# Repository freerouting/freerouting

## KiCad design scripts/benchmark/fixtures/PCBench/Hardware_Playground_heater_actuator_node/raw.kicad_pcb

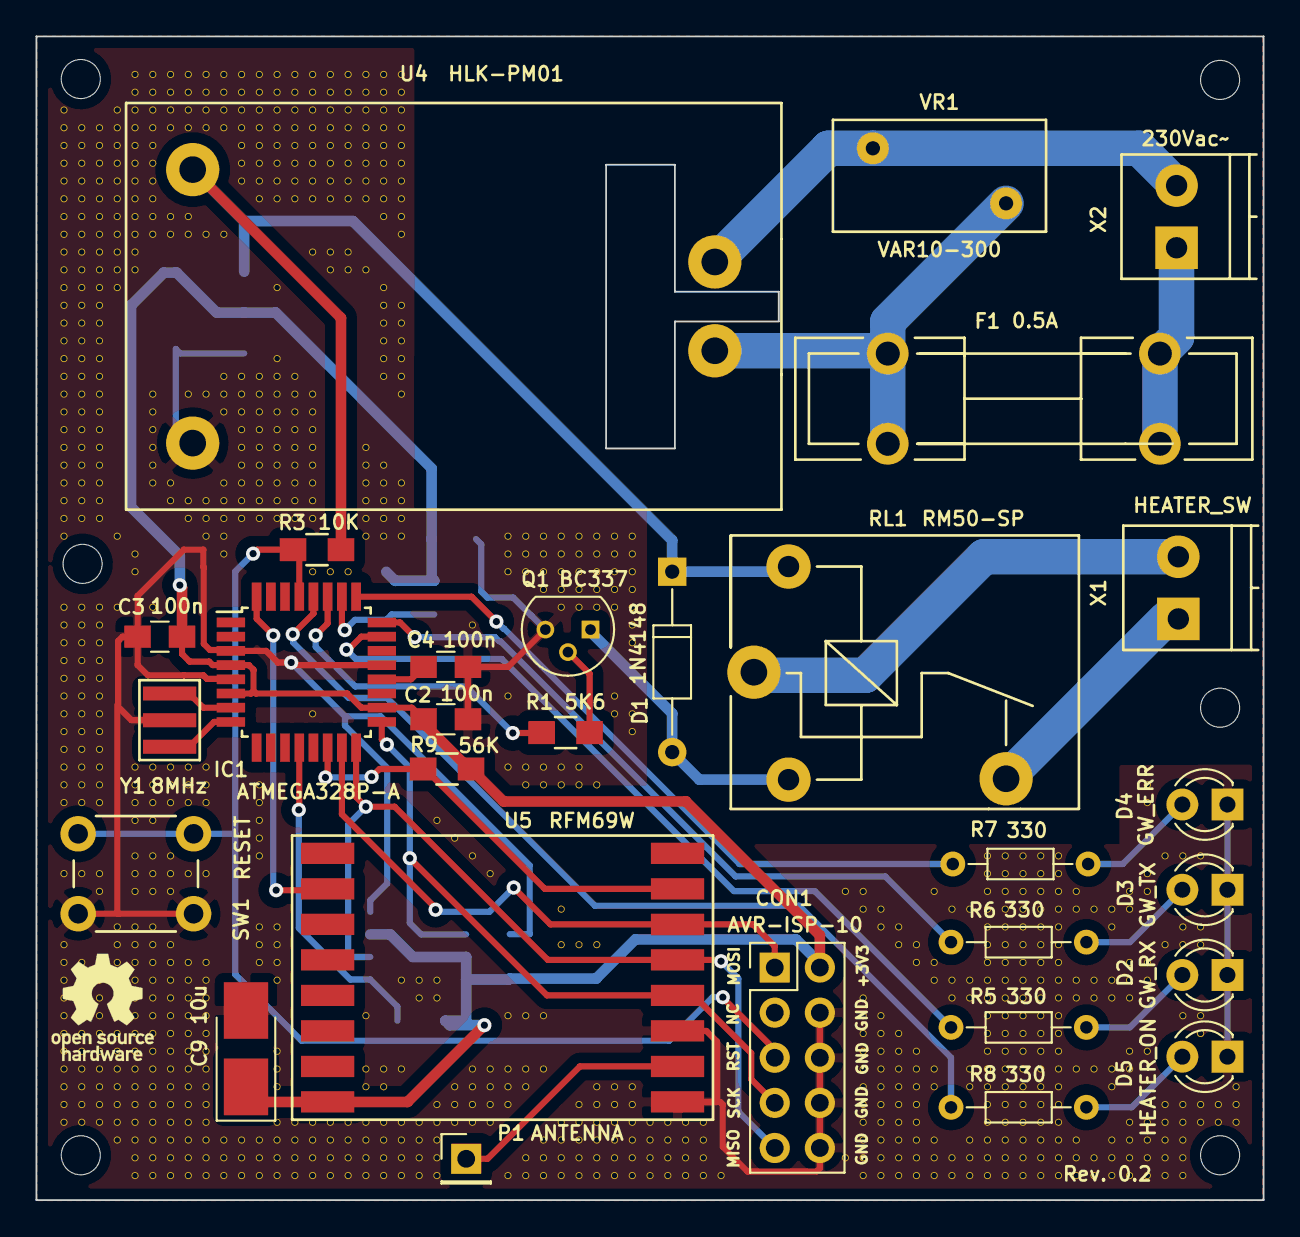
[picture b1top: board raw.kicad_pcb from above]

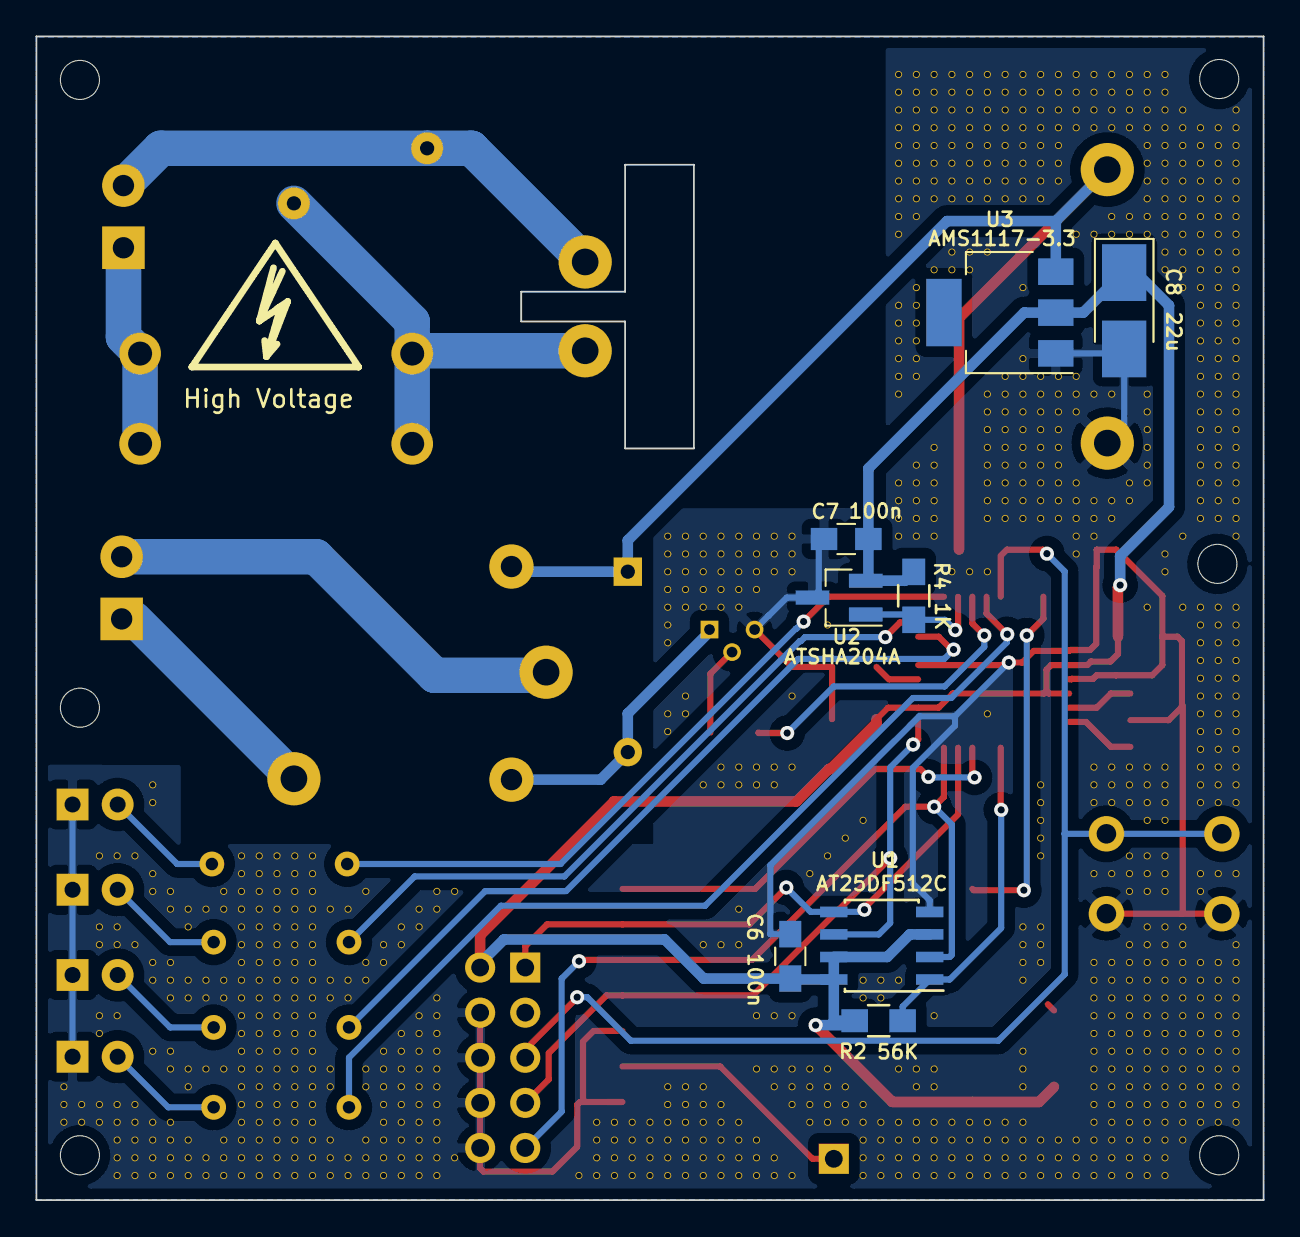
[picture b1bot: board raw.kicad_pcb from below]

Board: 2 copper layers, 69.1 x 65.5 mm, 982 parts (8 on the bottom side), 31 nets.

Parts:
C2, C3, C4, C6, C7: 100n; C_0805_HandSoldering
C8: 22u; CP_Tantalum_Case-B_EIA-3528-21_Hand
C9: 10u; CP_Tantalum_Case-B_EIA-3528-21_Hand
CON1: AVR-ISP-10; Pin_Header_Straight_2x05_Pitch2.54mm
D1: 1N4148; D_DO-35_SOD27_P10.16mm_Horizontal
D2: GW_RX; LED_D3.0mm
D3: GW_TX; LED_D3.0mm
D4: GW_ERR; LED_D3.0mm
D5: HEATER_ON; LED_D3.0mm
F1: 0.5A; Fuseholder5x20_horiz_open_lateral_Type-II
IC1: ATMEGA328P-A; TQFP-32_7x7mm_Pitch0.8mm
P1: ANTENNA; Pin_Header_Straight_1x01_Pitch2.54mm
Q1: BC337; TO-92_Molded_Narrow
R1: 5K6; R_0805_HandSoldering
R2, R9: 56K; R_0805_HandSoldering
R3: 10K; R_0805_HandSoldering
R4: 1K; R_0805_HandSoldering
R5, R6, R7, R8: 330; R_Axial_DIN0204_L3.6mm_D1.6mm_P7.62mm_Horizontal
RL1: RM50-SP; RM50_SP
SW1: RESET; SW_PUSH_6mm
U1: AT25DF512C; SOIC-8_3.9x4.9mm_Pitch1.27mm
U2: ATSHA204A; SOT-23_Handsoldering
U3: AMS1117-3.3; SOT-223
U4: HLK-PM01
U5: RFM69W; RFM69HW_SMD_Handsoldering
V10_6, V10_7, V10_8, V10_9, V10_10, V10_11, V10_12, V10_13, V10_14, V10_15, V10_16, V10_17, V10_18, V10_19, V10_20, V10_21, V10_22, V10_23, V10_24, V10_25, V10_26, V10_27, V10_28, V10_29, V10_30, V10_34, V10_35, V10_36, V10_37, V10_38, V10_39, V10_40, V10_41, V10_42, V10_43, V10_44, V10_45, V10_49, V10_53, V10_54, V10_55, V10_56, V10_57, V10_58, V10_59, V10_60, V10_61, V10_62, V10_63, V11_7, V11_8, V11_9, V11_10, V11_11, V11_12, V11_13, V11_14, V11_15, V11_16, V11_17, V11_18, V11_19, V11_20, V11_21, V11_22, V11_23, V11_24, V11_25, V11_26, V11_27, V11_28, V11_29, V11_34, V11_35, V11_36, V11_37, V11_38, V11_39, V11_40, V11_41, V11_42, V11_43, V11_44, V11_45, V11_49, V11_54, V11_55, V11_56, V11_57, V11_58, V11_59, V11_60, V11_61, V11_62, V11_63, V12_7, V12_8, V12_9, V12_10, V12_11, V12_12, V12_13, V12_14, V12_15, V12_16, V12_17, V12_18, V12_19, V12_20, V12_21, V12_22, V12_23, V12_24, V12_25, V12_26, V12_27, V12_28, V12_29, V12_34, V12_35, V12_36, V12_37, V12_38, V12_39, V12_40, V12_41, V12_42, V12_43, V12_44, V12_45, V12_49, V12_50, V12_54, V12_55, V12_56, V12_57, V12_58, V12_59, V12_60, V12_61, V12_62, V12_63, V13_6, V13_7, V13_8, V13_9, V13_10, V13_11, V13_12, V13_13, V13_14, V13_15, V13_16, V13_30, V13_34, V13_52, V13_53, V13_54, V13_55, V13_56, V13_57, V13_58, V13_59, V13_60, V13_61, V13_62, V13_63, V13_64, V14_4, V14_5, V14_6, V14_7, V14_8, V14_9, V14_10, V14_11, V14_12, V14_13, V14_14, V14_15, V14_31, V14_32, V14_43, V14_44, V14_45, V14_46, V14_48, V14_49, V14_50, V14_52, V14_53, V14_54, V14_55, V14_56, V14_57, V14_58, V14_59, V14_60, V14_61, V14_62, V14_63, V14_64, V14_65, V14_66, V15_4, V15_5, V15_6, V15_7, V15_8, V15_9, V15_10, V15_11, V15_12, V15_13, V15_22, V15_23, V15_24, V15_25, V15_26, V15_27, V15_34, V15_43, V15_44, V15_45, V15_46, V15_48, V15_49, V15_50, V15_52, V15_53, V15_54, V15_55, V15_56, V15_57, V15_58, V15_59, V15_60, V15_61, V15_62, V15_63, V15_64, V15_65, V15_66, V16_4, V16_5, V16_6, V16_7, V16_12, V16_13, V16_27, V16_28, V16_43, V16_44, V16_45, V16_48, V16_49, V16_50, V16_53, V16_54, V16_55, V16_56, V16_57, V16_58, V16_59, V16_60, V16_61, V16_62, V16_63, V16_64, V16_65, V16_66, V17_4, V17_5, V17_6, V17_7, V17_12, V17_13, V17_22, V17_28, V17_29, V17_43, V17_44, V17_45, V17_49, V17_54, V17_55, V17_56, V17_57, V17_58, V17_59, V17_60, V17_61, V17_62, V17_63, V17_64, V17_65, V17_66, V18_4, V18_5, V18_6, V18_7, V18_13, V18_22, V18_28, V18_29, V18_30, V18_43, V18_44, V18_45, V18_49, V18_54, V18_55, V18_56, V18_57, V18_58, V18_59, V18_60, V18_61, V18_62, V18_63, V18_64, V18_65, V18_66, V19_4, V19_5, V19_6, V19_7, V19_13, V19_21, V19_22, V19_23, V19_27, V19_28, V19_29, V19_30, V19_31, V19_64, V19_65, V19_66, V20_4, V20_5, V20_6, V20_7, V20_8, V20_9, V20_10, V20_21, V20_22, V20_23, V20_24, V20_25, V20_26, V20_27, V20_28, V20_29, V20_64, V20_65, V20_66, V21_4, V21_5, V21_6, V21_7, V21_8, V21_9, V21_10, V21_11, V21_21, V21_22, V21_23, V21_24, V21_25, V21_26, V21_27, V21_28, V21_29, V21_44, V21_45, V21_46, V21_47, V21_48, V21_52, V21_53, V21_54, V21_64, V21_65, V21_66, V22_4, V22_5, V22_6, V22_7, V22_8, V22_9, V22_10, V22_11, V22_16, V22_20, V22_21, V22_22, V22_23, V22_24, V22_25, V22_26, V22_27, V22_28, V22_29, V22_52, V22_53, V22_54, V22_55, V22_59, V22_60, V22_61, V22_63, V22_64, V22_65, V22_66, V23_4, V23_5, V23_6, V23_7, V23_8, V23_9, V23_10, V23_11, V23_21, V23_22, V23_23, V23_24, V23_25, V23_26, V23_27, V23_28, V23_29, V23_63, V23_64, V23_65, V23_66, V24_4, V24_5, V24_6, V24_7, V24_8, V24_9, V24_10, V24_11, V24_14, V24_22, V24_23, V24_24, V24_25, V24_26, V24_27, V24_28, V24_29, V24_32, V24_40, V24_63, V24_64, V24_65, V24_66, V25_4, V25_5, V25_6, V25_7, V25_8, V25_9, V25_10, V25_11, V25_14, V25_15, V25_32, V25_63, V25_64, V25_65, V25_66, V26_4, V26_5, V26_6, V26_7, V26_8, V26_9, V26_10, V26_11, V26_14, V26_15, V26_32, V26_63, V26_64, V26_65, V26_66, V27_4, V27_5, V27_6, V27_7, V27_8, V27_9, V27_10, V27_11, V27_15, V27_25, V27_26, V27_27, V27_28, V27_29, V27_30, V27_57, V27_60, V27_61, V27_63, V27_64, V27_65, V27_66, V28_4, V28_5, V28_6, V28_7, V28_8, V28_9, V28_10, V28_11, V28_12, V28_16, V28_17, V28_18, V28_19, V28_20, V28_21, V28_26, V28_27, V28_28, V28_29, V28_30, V28_60, V28_61, V28_63, V28_64, V28_65, V28_66, V29_4, V29_5, V29_6, V29_7, V29_8, V29_9, V29_10, V29_11, V29_12, V29_13, V29_17, V29_18, V29_19, V29_20, V29_21, V29_22, V29_27, V29_28, V29_29, V29_30, V29_55, V29_60, V29_63, V29_64, V29_65, V29_66, V30_55, V30_56, V30_63, V30_64, V30_65, V30_66, V31_46, V31_55, V31_56, V31_62, V31_63, V31_64, V31_65, V31_66, V32_47, V32_61, V32_62, V32_63, V33_35, V33_48, V33_60, V33_61, V33_62, V33_63, V34_49, V34_60, V34_61, V34_62, V34_63, V35_30, V35_31, V35_32, V35_39, V35_43, V35_57, V35_60, V35_61, V35_62, V35_66, V36_30, V36_31, V36_32, V36_43, V36_44, V36_57, V36_60, V36_61, V36_65, V36_66, V37_30, V37_31, V37_32, V37_33, V37_43, V37_44, V37_57, V37_60, V37_64, V37_65, V37_66, V38_30, V38_31, V38_32, V38_33, V38_34, V38_43, V38_44, V38_51, V38_53, V38_63, V38_64, V38_65, V38_66, V39_30, V39_31, V39_32, V39_33, V39_34, V39_43, V39_44, V39_53, V39_62, V39_63, V39_64, V39_65, V39_66, V40_30, V40_31, V40_32, V40_33, V40_34, V40_44, V40_53, V40_61, V40_62, V40_63, V40_64, V40_65, V40_66, V41_30, V41_31, V41_32, V41_33, V41_34, V41_39, V41_40, V41_61, V41_62, V41_63, V41_64, V41_65, V41_66, V42_30, V42_31, V42_32, V42_33, V42_34, V42_35, V42_36, V42_40, V42_41, V42_61, V42_62, V42_63, V42_64, V42_65, V42_66, V43_63, V43_64, V43_65, V43_66, V44_63, V44_64, V44_65, V44_66, V45_63, V45_64, V45_65, V45_66, V46_63, V46_64, V46_65, V46_66, V47_66, V54_50, V54_65, V55_50, V55_51, V55_56, V55_57, V55_58, V55_59, V55_60, V55_61, V55_62, V55_63, V55_64, V55_65, V55_66, V56_51, V56_52, V56_57, V56_58, V56_59, V56_60, V56_61, V56_62, V56_63, V56_64, V56_65, V56_66, V57_52, V57_53, V57_58, V57_59, V57_60, V57_61, V57_62, V57_63, V57_64, V57_65, V57_66, V58_53, V58_54, V58_59, V58_60, V58_61, V58_62, V58_63, V58_64, V58_65, V58_66, V59_50, V59_54, V59_55, V59_60, V59_61, V59_64, V59_65, V59_66, V60_51, V60_55, V60_56, V60_65, V60_66, V61_51, V61_55, V61_56, V61_60, V61_61, V61_64, V61_65, V61_66, V62_48, V62_49, V62_50, V62_51, V62_52, V62_53, V62_54, V62_55, V62_56, V62_57, V62_58, V62_59, V62_60, V62_61, V62_62, V62_63, V62_64, V62_65, V62_66, V63_48, V63_49, V63_50, V63_51, V63_52, V63_53, V63_54, V63_55, V63_56, V63_57, V63_58, V63_59, V63_60, V63_61, V63_62, V63_63, V63_64, V63_65, V63_66, V64_48, V64_49, V64_50, V64_51, V64_52, V64_53, V64_54, V64_55, V64_56, V64_57, V64_58, V64_59, V64_60, V64_61, V64_62, V64_63, V64_64, V64_65, V64_66, V65_48, V65_49, V65_50, V65_51, V65_52, V65_53, V65_54, V65_55, V65_56, V65_57, V65_58, V65_59, V65_60, V65_61, V65_62, V65_63, V65_64, V65_65, V65_66, V66_48, V66_49, V66_50, V66_51, V66_52, V66_53, V66_54, V66_55, V66_56, V66_57, V66_58, V66_59, V66_60, V66_61, V66_62, V66_63, V66_64, V66_65, V66_66, V67_50, V67_51, V67_55, V67_56, V67_60, V67_64, V67_65, V67_66, V68_51, V68_55, V68_56, V68_60, V68_65, V68_66, V69_51, V69_52, V69_55, V69_56, V69_60, V69_61, V69_64, V69_65, V69_66, V70_50, V70_51, V70_54, V70_55, V70_56, V70_59, V70_60, V70_63, V70_64, V70_65, V70_66, V71_44, V71_45, V71_49, V71_50, V71_54, V71_55, V71_59, V71_63, V71_64, V71_65, V71_66, V72_48, V72_53, V72_62, V72_63, V72_64, V72_65, V72_66, V73_48, V73_52, V73_53, V73_57, V73_62, V73_63, V73_64, V73_65, V73_66, V74_48, V74_52, V74_53, V74_57, V74_58, V74_62, V74_63, V75_62, V75_63, V76_61, V76_62, V76_63: AUTO_VIA; VIA_MATRIX
VR1: VAR10-300; RV_Disc_D12_W6.3_P7.5
X1: HEATER_SW; TerminalBlock_Pheonix_PT-3.5mm_2pol
X2: 230Vac~~; TerminalBlock_Pheonix_PT-3.5mm_2pol
Y1: 8MHz; ZTTCR-3

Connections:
+3V3: C2.2, C3.2, C6.1, C7.1, C8.1, C9.1, CON1.2, IC1.4, IC1.6, IC1.18, R2.2, R4.2, R9.2, U1.3, U1.7, U1.8, U2.2, U3.2, U5.8
+5V: D1.1, R3.1, RL1.A1, U3.3, U4.3
/ATSHA204A: IC1.26, R4.1, U2.1
/ERR_LED: IC1.25, R7.2
/HEATER_ON_LED: IC1.28, R8.2
/H_RELAY_CMD: IC1.27, R1.2
/MISO: CON1.9, IC1.16, U1.2, U5.13
/MOSI: CON1.1, IC1.15, U1.5, U5.14
/RFM69W_INT: IC1.32, U5.2
/RFM69W_SS: IC1.14, R9.1, U5.15
/RST: CON1.5, IC1.29, R3.2, SW1.1
/RX_LED: IC1.23, R5.2
/SCK: CON1.7, IC1.17, U1.6, U5.12
/SPI_FLASH_SS: IC1.12, R2.1, U1.1
/TX_LED: IC1.24, R6.2
GND: C2.1, C3.1, C4.1, C6.2, C7.2, C8.2, C9.2, CON1.4, CON1.6, CON1.8, CON1.10, D2.1, D3.1, D4.1, D5.1, IC1.3, IC1.5, IC1.21, Q1.3, SW1.2, U1.4, U2.3, U3.1, U4.4, U5.9, U5.11, V10_6.1, V10_7.1, V10_8.1, V10_9.1, V10_10.1, V10_11.1, V10_12.1, V10_13.1, V10_14.1, V10_15.1, V10_16.1, V10_17.1, V10_18.1, V10_19.1, V10_20.1, V10_21.1, V10_22.1, V10_23.1, V10_24.1, V10_25.1, V10_26.1, V10_27.1, V10_28.1, V10_29.1, V10_30.1, V10_34.1, V10_35.1, V10_36.1, V10_37.1, V10_38.1, V10_39.1, V10_40.1, V10_41.1, V10_42.1, V10_43.1, V10_44.1, V10_45.1, V10_49.1, V10_53.1, V10_54.1, V10_55.1, V10_56.1, V10_57.1, V10_58.1, V10_59.1, V10_60.1, V10_61.1, V10_62.1, V10_63.1, V11_7.1, V11_8.1, V11_9.1, V11_10.1, V11_11.1, V11_12.1, V11_13.1, V11_14.1, V11_15.1, V11_16.1, V11_17.1, V11_18.1, V11_19.1, V11_20.1, V11_21.1, V11_22.1, V11_23.1, V11_24.1, V11_25.1, V11_26.1, V11_27.1, V11_28.1, V11_29.1, V11_34.1, V11_35.1, V11_36.1, V11_37.1, V11_38.1, V11_39.1, V11_40.1, V11_41.1, V11_42.1, V11_43.1, V11_44.1, V11_45.1, V11_49.1, V11_54.1, V11_55.1, V11_56.1, V11_57.1, V11_58.1, V11_59.1, V11_60.1, V11_61.1, V11_62.1, V11_63.1, V12_7.1, V12_8.1, V12_9.1, V12_10.1, V12_11.1, V12_12.1, V12_13.1, V12_14.1, V12_15.1, V12_16.1, V12_17.1, V12_18.1, V12_19.1, V12_20.1, V12_21.1, V12_22.1, V12_23.1, V12_24.1, V12_25.1, V12_26.1, V12_27.1, V12_28.1, V12_29.1, V12_34.1, V12_35.1, V12_36.1, V12_37.1, V12_38.1, V12_39.1, V12_40.1, V12_41.1, V12_42.1, V12_43.1, V12_44.1, V12_45.1, V12_49.1, V12_50.1, V12_54.1, V12_55.1, V12_56.1, V12_57.1, V12_58.1, V12_59.1, V12_60.1, V12_61.1, V12_62.1, V12_63.1, V13_6.1, V13_7.1, V13_8.1, V13_9.1, V13_10.1, V13_11.1, V13_12.1, V13_13.1, V13_14.1, V13_15.1, V13_16.1, V13_30.1, V13_34.1, V13_52.1, V13_53.1, V13_54.1, V13_55.1, V13_56.1, V13_57.1, V13_58.1, V13_59.1, V13_60.1, V13_61.1, V13_62.1, V13_63.1, V13_64.1, V14_4.1, V14_5.1, V14_6.1, V14_7.1, V14_8.1, V14_9.1, V14_10.1, V14_11.1, V14_12.1, V14_13.1, V14_14.1, V14_15.1, V14_31.1, V14_32.1, V14_43.1, V14_44.1, V14_45.1, V14_46.1, V14_48.1, V14_49.1, V14_50.1, V14_52.1, V14_53.1, V14_54.1, V14_55.1, V14_56.1, V14_57.1, V14_58.1, V14_59.1, V14_60.1, V14_61.1, V14_62.1, V14_63.1, V14_64.1, V14_65.1, V14_66.1, V15_4.1, V15_5.1, V15_6.1, V15_7.1, V15_8.1, V15_9.1, V15_10.1, V15_11.1, V15_12.1, V15_13.1, V15_22.1, V15_23.1, V15_24.1, V15_25.1, V15_26.1, V15_27.1, V15_34.1, V15_43.1, V15_44.1, V15_45.1, V15_46.1, V15_48.1, V15_49.1, V15_50.1, V15_52.1, V15_53.1, V15_54.1, V15_55.1, V15_56.1, V15_57.1, V15_58.1, V15_59.1, V15_60.1, V15_61.1, V15_62.1, V15_63.1, V15_64.1, V15_65.1, V15_66.1, V16_4.1, V16_5.1, V16_6.1, V16_7.1, V16_12.1, V16_13.1, V16_27.1, V16_28.1, V16_43.1, V16_44.1, V16_45.1, V16_48.1, V16_49.1, V16_50.1, V16_53.1, V16_54.1, V16_55.1, V16_56.1, V16_57.1, V16_58.1, V16_59.1, V16_60.1, V16_61.1, V16_62.1, V16_63.1, V16_64.1, V16_65.1, V16_66.1, V17_4.1, V17_5.1, V17_6.1, V17_7.1, V17_12.1, V17_13.1, V17_22.1, V17_28.1, V17_29.1, V17_43.1, V17_44.1, V17_45.1, V17_49.1, V17_54.1, V17_55.1, V17_56.1, V17_57.1, V17_58.1, V17_59.1, V17_60.1, V17_61.1, V17_62.1, V17_63.1, V17_64.1, V17_65.1, V17_66.1, V18_4.1, V18_5.1, V18_6.1, V18_7.1, V18_13.1, V18_22.1, V18_28.1, V18_29.1, V18_30.1, V18_43.1, V18_44.1, V18_45.1, V18_49.1, V18_54.1, V18_55.1, V18_56.1, V18_57.1, V18_58.1, V18_59.1, V18_60.1, V18_61.1, V18_62.1, V18_63.1, V18_64.1, V18_65.1, V18_66.1, V19_4.1, V19_5.1, V19_6.1, V19_7.1, V19_13.1, V19_21.1, V19_22.1, V19_23.1, V19_27.1, V19_28.1, V19_29.1, V19_30.1, V19_31.1, V19_64.1, V19_65.1, V19_66.1, V20_4.1, V20_5.1, V20_6.1, V20_7.1, V20_8.1, V20_9.1, V20_10.1, V20_21.1, V20_22.1, V20_23.1, V20_24.1, V20_25.1, V20_26.1, V20_27.1, V20_28.1, V20_29.1, V20_64.1, V20_65.1, V20_66.1, V21_4.1, V21_5.1, V21_6.1, V21_7.1, V21_8.1, V21_9.1, V21_10.1, V21_11.1, V21_21.1, V21_22.1, V21_23.1, V21_24.1, V21_25.1, V21_26.1, V21_27.1, V21_28.1, V21_29.1, V21_44.1, V21_45.1, V21_46.1, V21_47.1, V21_48.1, V21_52.1, V21_53.1, V21_54.1, V21_64.1, V21_65.1, V21_66.1, V22_4.1, V22_5.1, V22_6.1, V22_7.1, V22_8.1, V22_9.1, V22_10.1, V22_11.1, V22_16.1, V22_20.1, V22_21.1, V22_22.1, V22_23.1, V22_24.1, V22_25.1, V22_26.1, V22_27.1, V22_28.1, V22_29.1, V22_52.1, V22_53.1, V22_54.1, V22_55.1, V22_59.1, V22_60.1, V22_61.1, V22_63.1, V22_64.1, V22_65.1, V22_66.1, V23_4.1, V23_5.1, V23_6.1, V23_7.1, V23_8.1, V23_9.1, V23_10.1, V23_11.1, V23_21.1, V23_22.1, V23_23.1, V23_24.1, V23_25.1, V23_26.1, V23_27.1, V23_28.1, V23_29.1, V23_63.1, V23_64.1, V23_65.1, V23_66.1, V24_4.1, V24_5.1, V24_6.1, V24_7.1, V24_8.1, V24_9.1, V24_10.1, V24_11.1, V24_14.1, V24_22.1, V24_23.1, V24_24.1, V24_25.1, V24_26.1, V24_27.1, V24_28.1, V24_29.1, V24_32.1, V24_40.1, V24_63.1, V24_64.1, V24_65.1, V24_66.1, V25_4.1, V25_5.1, V25_6.1, V25_7.1, V25_8.1, V25_9.1, V25_10.1, V25_11.1, V25_14.1, V25_15.1, V25_32.1, V25_63.1, V25_64.1, V25_65.1, V25_66.1, V26_4.1, V26_5.1, V26_6.1, V26_7.1, V26_8.1, V26_9.1, V26_10.1, V26_11.1, V26_14.1, V26_15.1, V26_32.1, V26_63.1, V26_64.1, V26_65.1, V26_66.1, V27_4.1, V27_5.1, V27_6.1, V27_7.1, V27_8.1, V27_9.1, V27_10.1, V27_11.1, V27_15.1, V27_25.1, V27_26.1, V27_27.1, V27_28.1, V27_29.1, V27_30.1, V27_57.1, V27_60.1, V27_61.1, V27_63.1, V27_64.1, V27_65.1, V27_66.1, V28_4.1, V28_5.1, V28_6.1, V28_7.1, V28_8.1, V28_9.1, V28_10.1, V28_11.1, V28_12.1, V28_16.1, V28_17.1, V28_18.1, V28_19.1, V28_20.1, V28_21.1, V28_26.1, V28_27.1, V28_28.1, V28_29.1, V28_30.1, V28_60.1, V28_61.1, V28_63.1, V28_64.1, V28_65.1, V28_66.1, V29_4.1, V29_5.1, V29_6.1, V29_7.1, V29_8.1, V29_9.1, V29_10.1, V29_11.1, V29_12.1, V29_13.1, V29_17.1, V29_18.1, V29_19.1, V29_20.1, V29_21.1, V29_22.1, V29_27.1, V29_28.1, V29_29.1, V29_30.1, V29_55.1, V29_60.1, V29_63.1, V29_64.1, V29_65.1, V29_66.1, V30_55.1, V30_56.1, V30_63.1, V30_64.1, V30_65.1, V30_66.1, V31_46.1, V31_55.1, V31_56.1, V31_62.1, V31_63.1, V31_64.1, V31_65.1, V31_66.1, V32_47.1, V32_61.1, V32_62.1, V32_63.1, V33_35.1, V33_48.1, V33_60.1, V33_61.1, V33_62.1, V33_63.1, V34_49.1, V34_60.1, V34_61.1, V34_62.1, V34_63.1, V35_30.1, V35_31.1, V35_32.1, V35_39.1, V35_43.1, V35_57.1, V35_60.1, V35_61.1, V35_62.1, V35_66.1, V36_30.1, V36_31.1, V36_32.1, V36_43.1, V36_44.1, V36_57.1, V36_60.1, V36_61.1, V36_65.1, V36_66.1, V37_30.1, V37_31.1, V37_32.1, V37_33.1, V37_43.1, V37_44.1, V37_57.1, V37_60.1, V37_64.1, V37_65.1, V37_66.1, V38_30.1, V38_31.1, V38_32.1, V38_33.1, V38_34.1, V38_43.1, V38_44.1, V38_51.1, V38_53.1, V38_63.1, V38_64.1, V38_65.1, V38_66.1, V39_30.1, V39_31.1, V39_32.1, V39_33.1, V39_34.1, V39_43.1, V39_44.1, V39_53.1, V39_62.1, V39_63.1, V39_64.1, V39_65.1, V39_66.1, V40_30.1, V40_31.1, V40_32.1, V40_33.1, V40_34.1, V40_44.1, V40_53.1, V40_61.1, V40_62.1, V40_63.1, V40_64.1, V40_65.1, V40_66.1, V41_30.1, V41_31.1, V41_32.1, V41_33.1, V41_34.1, V41_39.1, V41_40.1, V41_61.1, V41_62.1, V41_63.1, V41_64.1, V41_65.1, V41_66.1, V42_30.1, V42_31.1, V42_32.1, V42_33.1, V42_34.1, V42_35.1, V42_36.1, V42_40.1, V42_41.1, V42_61.1, V42_62.1, V42_63.1, V42_64.1, V42_65.1, V42_66.1, V43_63.1, V43_64.1, V43_65.1, V43_66.1, V44_63.1, V44_64.1, V44_65.1, V44_66.1, V45_63.1, V45_64.1, V45_65.1, V45_66.1, V46_63.1, V46_64.1, V46_65.1, V46_66.1, V47_66.1, V54_50.1, V54_65.1, V55_50.1, V55_51.1, V55_56.1, V55_57.1, V55_58.1, V55_59.1, V55_60.1, V55_61.1, V55_62.1, V55_63.1, V55_64.1, V55_65.1, V55_66.1, V56_51.1, V56_52.1, V56_57.1, V56_58.1, V56_59.1, V56_60.1, V56_61.1, V56_62.1, V56_63.1, V56_64.1, V56_65.1, V56_66.1, V57_52.1, V57_53.1, V57_58.1, V57_59.1, V57_60.1, V57_61.1, V57_62.1, V57_63.1, V57_64.1, V57_65.1, V57_66.1, V58_53.1, V58_54.1, V58_59.1, V58_60.1, V58_61.1, V58_62.1, V58_63.1, V58_64.1, V58_65.1, V58_66.1, V59_50.1, V59_54.1, V59_55.1, V59_60.1, V59_61.1, V59_64.1, V59_65.1, V59_66.1, V60_51.1, V60_55.1, V60_56.1, V60_65.1, V60_66.1, V61_51.1, V61_55.1, V61_56.1, V61_60.1, V61_61.1, V61_64.1, V61_65.1, V61_66.1, V62_48.1, V62_49.1, V62_50.1, V62_51.1, V62_52.1, V62_53.1, V62_54.1, V62_55.1, V62_56.1, V62_57.1, V62_58.1, V62_59.1, V62_60.1, V62_61.1, V62_62.1, V62_63.1, V62_64.1, V62_65.1, V62_66.1, V63_48.1, V63_49.1, V63_50.1, V63_51.1, V63_52.1, V63_53.1, V63_54.1, V63_55.1, V63_56.1, V63_57.1, V63_58.1, V63_59.1, V63_60.1, V63_61.1, V63_62.1, V63_63.1, V63_64.1, V63_65.1, V63_66.1, V64_48.1, V64_49.1, V64_50.1, V64_51.1, V64_52.1, V64_53.1, V64_54.1, V64_55.1, V64_56.1, V64_57.1, V64_58.1, V64_59.1, V64_60.1, V64_61.1, V64_62.1, V64_63.1, V64_64.1, V64_65.1, V64_66.1, V65_48.1, V65_49.1, V65_50.1, V65_51.1, V65_52.1, V65_53.1, V65_54.1, V65_55.1, V65_56.1, V65_57.1, V65_58.1, V65_59.1, V65_60.1, V65_61.1, V65_62.1, V65_63.1, V65_64.1, V65_65.1, V65_66.1, V66_48.1, V66_49.1, V66_50.1, V66_51.1, V66_52.1, V66_53.1, V66_54.1, V66_55.1, V66_56.1, V66_57.1, V66_58.1, V66_59.1, V66_60.1, V66_61.1, V66_62.1, V66_63.1, V66_64.1, V66_65.1, V66_66.1, V67_50.1, V67_51.1, V67_55.1, V67_56.1, V67_60.1, V67_64.1, V67_65.1, V67_66.1, V68_51.1, V68_55.1, V68_56.1, V68_60.1, V68_65.1, V68_66.1, V69_51.1, V69_52.1, V69_55.1, V69_56.1, V69_60.1, V69_61.1, V69_64.1, V69_65.1, V69_66.1, V70_50.1, V70_51.1, V70_54.1, V70_55.1, V70_56.1, V70_59.1, V70_60.1, V70_63.1, V70_64.1, V70_65.1, V70_66.1, V71_44.1, V71_45.1, V71_49.1, V71_50.1, V71_54.1, V71_55.1, V71_59.1, V71_63.1, V71_64.1, V71_65.1, V71_66.1, V72_48.1, V72_53.1, V72_62.1, V72_63.1, V72_64.1, V72_65.1, V72_66.1, V73_48.1, V73_52.1, V73_53.1, V73_57.1, V73_62.1, V73_63.1, V73_64.1, V73_65.1, V73_66.1, V74_48.1, V74_52.1, V74_53.1, V74_57.1, V74_58.1, V74_62.1, V74_63.1, V75_62.1, V75_63.1, V76_61.1, V76_62.1, V76_63.1, Y1.2
unnamed: C4.2, IC1.20
unnamed: D1.2, Q1.1, RL1.A2
unnamed: D2.2, R5.1
unnamed: D3.2, R6.1
unnamed: D4.2, R7.1
unnamed: D5.2, R8.1
unnamed: F1.1, U4.1, VR1.1
unnamed: F1.2, X2.1
unnamed: IC1.7, Y1.3
unnamed: IC1.8, Y1.1
unnamed: P1.1, U5.10
unnamed: Q1.2, R1.1
unnamed: RL1.11, X1.2
unnamed: RL1.14, X1.1
unnamed: U4.2, VR1.2, X2.2

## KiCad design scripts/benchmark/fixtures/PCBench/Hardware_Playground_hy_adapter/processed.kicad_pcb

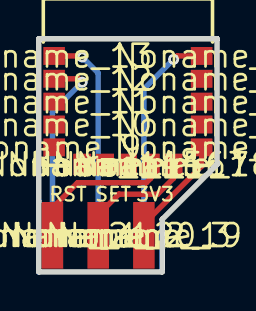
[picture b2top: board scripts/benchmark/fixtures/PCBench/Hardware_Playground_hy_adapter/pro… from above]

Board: 2 copper layers, 9.9 x 13.0 mm, 22 parts (0 on the bottom side), 6 nets.

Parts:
LG1: my_logo; gge4630
Noname_1, Noname_2, Noname_3, Noname_19, Noname_20, Noname_21: Pad_3.70mm
Noname_4, Noname_5, Noname_6, Noname_7, Noname_8, Noname_9, Noname_10, Noname_11, Noname_12, Noname_13, Noname_14, Noname_15, Noname_16, Noname_17, Noname_18: Pad_1.20mm

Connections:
S$340: Noname_17.14, Noname_21.1
S$342: Noname_18.15, Noname_20.1
S$344: Noname_4.10, Noname_19.1
S$346: Noname_1.1, Noname_12.2
S$350: Noname_2.1, Noname_13.1
S$354: Noname_3.1, Noname_8.6

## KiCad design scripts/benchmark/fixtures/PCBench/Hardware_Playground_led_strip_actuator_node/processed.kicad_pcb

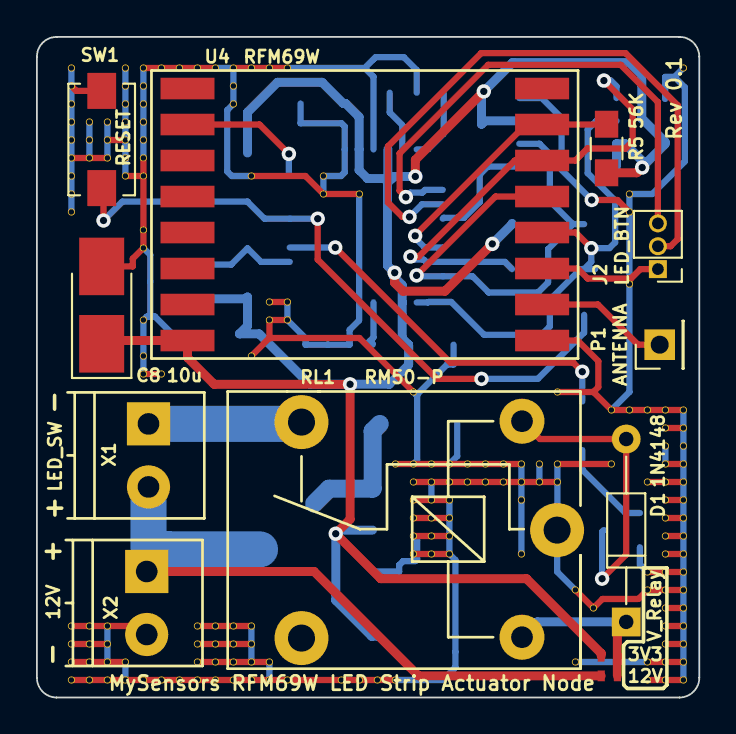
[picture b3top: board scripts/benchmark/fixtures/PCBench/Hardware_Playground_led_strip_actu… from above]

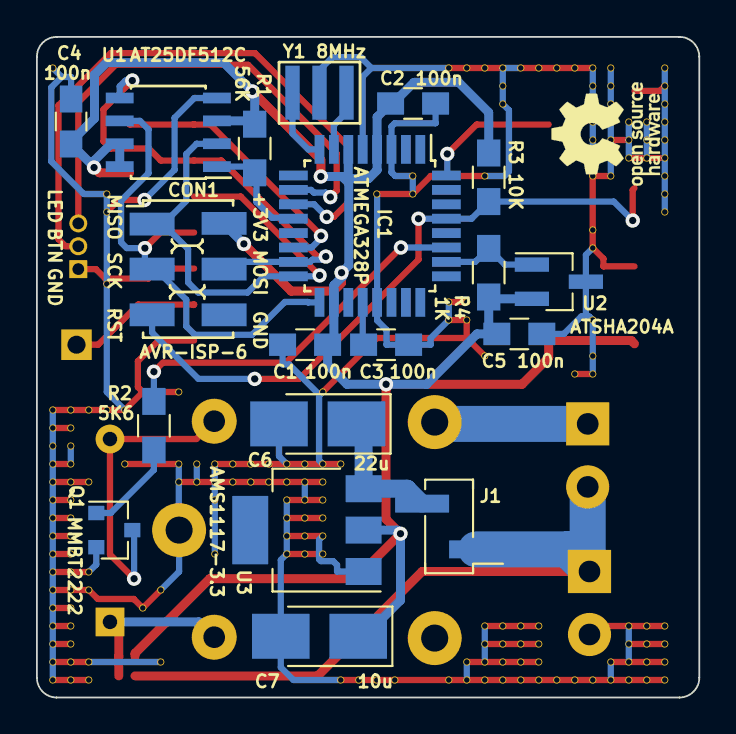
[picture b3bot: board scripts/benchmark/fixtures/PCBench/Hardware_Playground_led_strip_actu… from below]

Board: 2 copper layers, 36.8 x 36.7 mm, 208 parts (19 on the bottom side), 23 nets.

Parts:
C1, C2, C3, C4, C5: 100n; C_0805_HandSoldering
C6: 22u; CP_Tantalum_Case-B_EIA-3528-21_Hand
C7, C8: 10u; CP_Tantalum_Case-B_EIA-3528-21_Hand
CON1: AVR-ISP-6; AVR_ISP_SMT_Small_02x03
D1: 1N4148; D_DO-35_SOD27_P10.16mm_Horizontal
IC1: ATMEGA328P; TQFP-32_7x7mm_Pitch0.8mm
J1: EXT_DC_DC; Pin_Header_Straight_1x02_Pitch2.54mm_SMD_Pin1Left
J2: LED_BTN; Pin_Header_Straight_1x03_Pitch1.27mm
JP1: 3V3; R_0402_NoSilk
JP2: 12V; R_0402_NoSilk
P1: ANTENNA; Pin_Header_Straight_1x01_Pitch2.54mm
Q1: MMBT2222; SOT-23
R1, R5: 56K; R_0805_HandSoldering
R2: 5K6; R_0805_HandSoldering
R3: 10K; R_0805_HandSoldering
R4: 1K; R_0805_HandSoldering
RL1: RM50-P; RM50_P
SW1: RESET; SW_SPST_EVQPE1
U1: AT25DF512C; SOIC-8_3.9x4.9mm_Pitch1.27mm
U2: ATSHA204A; SOT-23_Handsoldering
U3: AMS1117-3.3; SOT-223
U4: RFM69W; RFM69HW_SMD_Handsoldering
V2_10, V2_11, V2_12, V2_13, V2_14, V2_15, V2_16, V2_17, V2_18, V2_41, V2_42, V2_43, V2_44, V3_13, V3_14, V3_15, V3_41, V3_42, V3_43, V3_44, V4_13, V4_14, V4_15, V4_41, V4_42, V4_43, V4_44, V5_10, V5_11, V5_12, V5_13, V5_14, V5_15, V5_16, V5_43, V5_44, V6_10, V6_11, V6_12, V6_13, V6_14, V6_15, V6_16, V6_19, V6_20, V6_24, V6_26, V6_27, V6_44, V7_10, V7_27, V7_44, V8_10, V8_44, V9_10, V9_41, V9_42, V9_43, V9_44, V10_10, V10_41, V10_42, V10_43, V10_44, V11_10, V11_11, V11_12, V11_41, V11_42, V11_43, V11_44, V12_10, V12_16, V12_26, V12_41, V12_42, V12_43, V12_44, V13_10, V13_23, V13_24, V13_43, V13_44, V14_10, V14_23, V14_24, V14_44, V16_16, V16_17, V17_44, V18_17, V18_44, V19_44, V20_32, V20_44, V21_28, V21_32, V21_33, V21_34, V21_35, V21_36, V21_37, V22_32, V22_33, V22_34, V22_35, V22_36, V22_37, V23_32, V23_33, V23_34, V23_35, V23_36, V23_37, V24_32, V24_33, V25_32, V25_33, V26_32, V26_33, V27_32, V27_33, V27_34, V27_37, V28_32, V28_33, V29_28, V29_32, V29_33, V30_39, V30_43, V31_40, V32_29, V32_32, V33_17, V33_18, V33_22, V33_29, V34_29, V34_33, V34_38, V34_39, V34_43, V34_44, V35_29, V35_30, V35_31, V35_32, V35_33, V35_34, V35_35, V35_36, V35_37, V35_38, V35_39, V35_40, V35_41, V35_42, V35_43, V35_44, V36_10, V36_29, V36_30, V36_31, V36_32, V36_33, V36_34, V36_35, V36_36, V36_37, V36_38, V36_39, V36_40, V36_41, V36_42, V36_43, V36_44: AUTO_VIA; VIA_MATRIX
X1: LED_SW; TerminalBlock_Pheonix_PT-3.5mm_2pol
X2: 12V; TerminalBlock_Pheonix_PT-3.5mm_2pol
Y1: 8MHz; ZTTCR-3

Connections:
+3V3: C1.2, C2.2, C4.1, C5.1, C7.1, C8.1, CON1.2, IC1.4, IC1.6, IC1.18, JP1.1, R1.2, R3.1, R4.2, R5.2, U1.3, U1.7, U1.8, U2.2, U3.2, U4.8
/ATSHA204A: IC1.26, R4.1, U2.1
/LED_12V: J1.1, JP2.2, X1.2, X2.1
/LED_BTN: IC1.11, J2.2
/LED_BTN_SIGNALING: IC1.10, J2.3
/LED_RELAY_CMD: IC1.27, R2.2
/MISO: CON1.1, IC1.16, U1.2, U4.13
/MOSI: CON1.4, IC1.15, U1.5, U4.14
/RFM69W_INT: IC1.32, U4.2
/RFM69W_SS: IC1.14, R5.1, U4.15
/RST: CON1.5, IC1.29, R3.2, SW1.1
/SCK: CON1.3, IC1.17, U1.6, U4.12
/SPI_FLASH_SS: IC1.12, R1.1, U1.1
GND: C1.1, C2.1, C3.1, C4.2, C5.2, C6.2, C7.2, C8.2, IC1.3, IC1.5, IC1.21, J2.1, Q1.2, RL1.11, SW1.2, U1.4, U2.3, U3.1, U4.9, U4.11, V2_10.1, V2_11.1, V2_12.1, V2_13.1, V2_14.1, V2_15.1, V2_16.1, V2_17.1, V2_18.1, V2_41.1, V2_42.1, V2_43.1, V2_44.1, V3_13.1, V3_14.1, V3_15.1, V3_41.1, V3_42.1, V3_43.1, V3_44.1, V4_13.1, V4_14.1, V4_15.1, V4_41.1, V4_42.1, V4_43.1, V4_44.1, V5_10.1, V5_11.1, V5_12.1, V5_13.1, V5_14.1, V5_15.1, V5_16.1, V5_43.1, V5_44.1, V6_10.1, V6_11.1, V6_12.1, V6_13.1, V6_14.1, V6_15.1, V6_16.1, V6_19.1, V6_20.1, V6_24.1, V6_26.1, V6_27.1, V6_44.1, V7_10.1, V7_27.1, V7_44.1, V8_10.1, V8_44.1, V9_10.1, V9_41.1, V9_42.1, V9_43.1, V9_44.1, V10_10.1, V10_41.1, V10_42.1, V10_43.1, V10_44.1, V11_10.1, V11_11.1, V11_12.1, V11_41.1, V11_42.1, V11_43.1, V11_44.1, V12_10.1, V12_16.1, V12_26.1, V12_41.1, V12_42.1, V12_43.1, V12_44.1, V13_10.1, V13_23.1, V13_24.1, V13_43.1, V13_44.1, V14_10.1, V14_23.1, V14_24.1, V14_44.1, V16_16.1, V16_17.1, V17_44.1, V18_17.1, V18_44.1, V19_44.1, V20_32.1, V20_44.1, V21_28.1, V21_32.1, V21_33.1, V21_34.1, V21_35.1, V21_36.1, V21_37.1, V22_32.1, V22_33.1, V22_34.1, V22_35.1, V22_36.1, V22_37.1, V23_32.1, V23_33.1, V23_34.1, V23_35.1, V23_36.1, V23_37.1, V24_32.1, V24_33.1, V25_32.1, V25_33.1, V26_32.1, V26_33.1, V27_32.1, V27_33.1, V27_34.1, V27_37.1, V28_32.1, V28_33.1, V29_28.1, V29_32.1, V29_33.1, V30_39.1, V30_43.1, V31_40.1, V32_29.1, V32_32.1, V33_17.1, V33_18.1, V33_22.1, V33_29.1, V34_29.1, V34_33.1, V34_38.1, V34_39.1, V34_43.1, V34_44.1, V35_29.1, V35_30.1, V35_31.1, V35_32.1, V35_33.1, V35_34.1, V35_35.1, V35_36.1, V35_37.1, V35_38.1, V35_39.1, V35_40.1, V35_41.1, V35_42.1, V35_43.1, V35_44.1, V36_10.1, V36_29.1, V36_30.1, V36_31.1, V36_32.1, V36_33.1, V36_34.1, V36_35.1, V36_36.1, V36_37.1, V36_38.1, V36_39.1, V36_40.1, V36_41.1, V36_42.1, V36_43.1, V36_44.1, X2.2, Y1.2
unnamed: C3.2, IC1.20
unnamed: C6.1, J1.2, U3.3
unnamed: D1.1, JP1.2, JP2.1, RL1.A1
unnamed: D1.2, Q1.3, RL1.A2
unnamed: IC1.7, Y1.3
unnamed: IC1.8, Y1.1
unnamed: P1.1, U4.10
unnamed: Q1.1, R2.1
unnamed: RL1.14, X1.1
